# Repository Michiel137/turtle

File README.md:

# Turtle Robot

Een rijdende robot gemaakt met 3D prints, goedkope onderdelen en geprogrammeerd in MicroPython.

Alle bestanden, inclusief deze beschrijving zijn op GitHub te vinden: https://github.com/Michiel137/turtle

## Start

De robot bevat alle bestanden die je nodig hebt, maar hij moet nog wel geconfigureerd worden om hem via WiFi te kunnen programmeren.

1. Sluit de robot met een USB kabel aan op de computer
1. Installeer de ontwikkelomgiving voor MicroPython: [Thonny](https://thonny.org/).
1. Open Thonny. Kies "Standard" voor "Initial Settings"
1. Klik rechtsonderin de statusbalk om de interpreter te configureren
1. Kies "MicroPython (Raspberry Pi Pico)" voor de interpreter
1. Kies "Board in FS mode @ COM..." voor de poort
1. Onderin de shell zie je nu een Python prompt. Je kan hier Python commando's uitvoeren
1. Open in Thonny het bestand boot.py van de robot: Bestand -> Open -> Raspberry Pi Pico -> boot.py
1. Haal van de laatste regel in het bestand de "#" weg en vervang \<SSID\> en \<PASSWORD\> met de WiFi netwerknaam en het WiFi wachtwoord
1. Sla het bestand op: Bestand -> Opslaan
1. Herstart de robot door op het Stop icoon te klikken (of Uitvoeren -> Stoppen/Opnieuw starten backend)
1. De robot maakt nu verbinding met het WiFi netwerk
1. In het shell scherm wordt het adres van de robot geprint achter "WebREPL server started on". Kopieer dit adres
1. Klik rechtsonderin de statusbalk om de interpreter te configureren: Selecteer "Configureren interpreter"
1. Vul bij "Port or WebREPL" het adres van de robot in, maar vervang "http://" door "ws://"
1. Vul voor het wachtwoord "geheim" in
1. OK
1. Thonny maakt nu verbinding via WiFi. De USB kabel is niet meer nodig
1. Op de robot staan een aantal scripts die je uit kan proberen: Bestand -> Open -> Raspberry Pi Pico
    - blink.py - klipper met de leds
    - noise.py - maak geluid
    - collision.py - rij rond en probeer botsingen te voorkomen
    - square.py - teken een vierkant
1. Nadat je het script geopend hebt kan je het met F5 uitvoeren (of Uitvoeren -> Voer huidige script uit)
1. Sommige scripts hebben geen einde. Je kan het script stoppen met Ctrl-C (of Uitvoeren -> Onderbreek uitvoering)
1. Probeer de scripts uit en pas ze aan!
1. Als je een idee hebt en een nieuw script wil maken, maak dan een nieuw bestand: Bestand -> Nieuw
    - Bestanden hoeven niet op de robot te staan om ze uit te voeren: Bestand -> Opslaan -> Deze computer
    - Het is een goed idee om voor een nieuw script te beginnen met een kopie van een bestaand script
    - als je een fout in het script hebt gemaakt wordt dat in het shell scherm getoond als je het script uitvoerd

## Problemen Oplossen

1. Zijn de batterijen leeg?
1. Als de verbinding van Thonny met de robot niet meer lijkt te werken, verbind dan opnieuw door rechtonderin de statusbalk te klikken en "MicroPython (Raspberry Pi Pico) ws://\<ip\>:8266" te kiezen

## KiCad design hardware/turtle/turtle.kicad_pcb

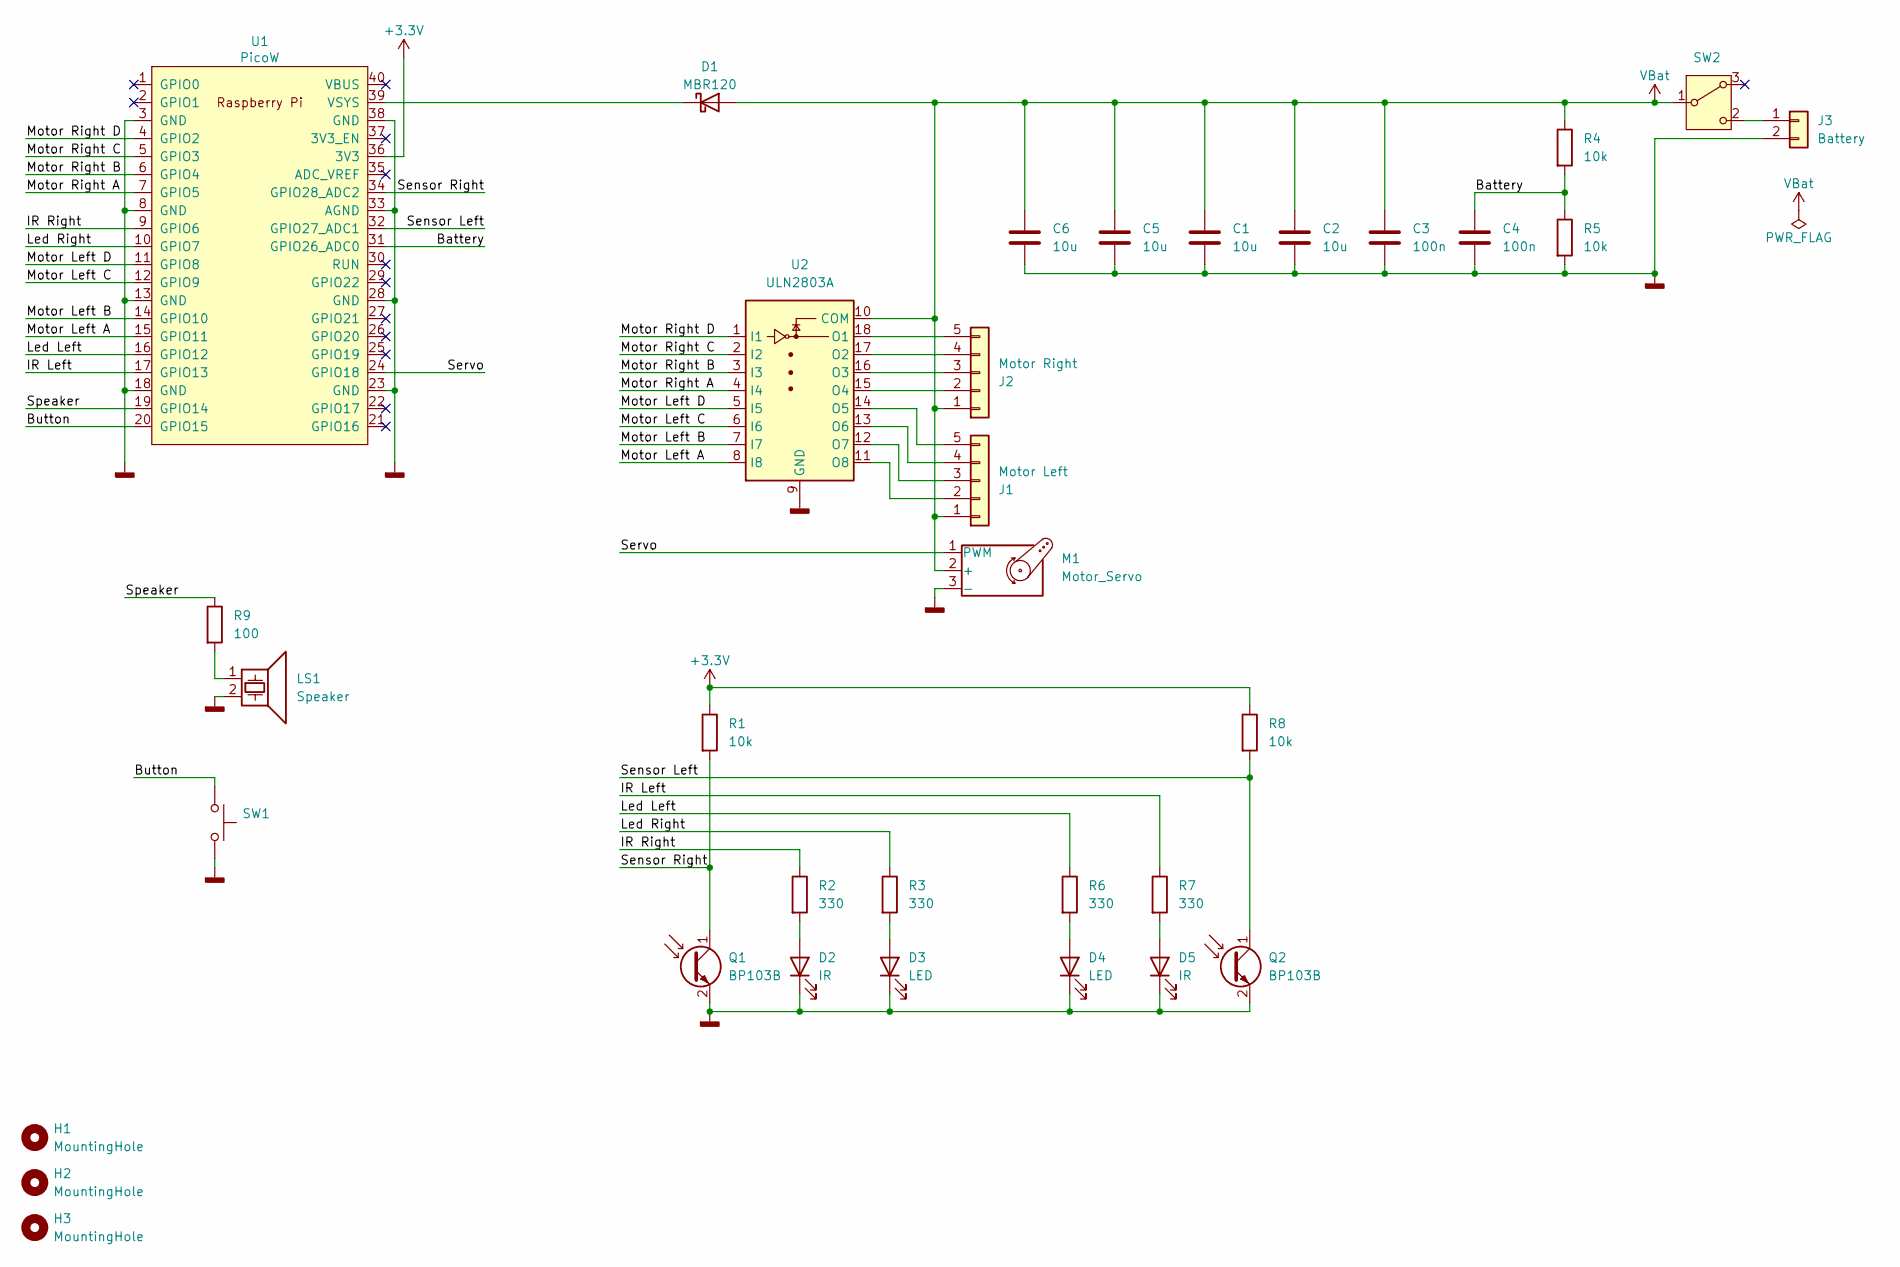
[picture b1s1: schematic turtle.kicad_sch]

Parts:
C1, C2, C5, C6: 10u; C_0603_1608Metric_Pad1.08x0.95mm_HandSolder
C3, C4: 100n; C_0603_1608Metric_Pad1.08x0.95mm_HandSolder
D1: MBR120; D_SOD-123F
D2, D5: IR; LED_D5.0mm_Horizontal_O1.27mm_Z3.0mm_truncated_silkscreen
D3, D4: LED; LED_D5.0mm_Horizontal_O1.27mm_Z3.0mm_truncated_silkscreen
H1, H2, H3: MountingHole; MountingHole_2.2mm_M2
J1: Motor Left; JST_EH_B5B-EH-A_1x05_P2.50mm_Vertical
J2: Motor Right; JST_EH_B5B-EH-A_1x05_P2.50mm_Vertical
J3: Battery; JST_EH_B2B-EH-A_1x02_P2.50mm_Vertical
LS1: Speaker; Buzzer_TDK_PS1240P02BT_D12.2mm_H6.5mm
M1: Motor_Servo; PinHeader_1x03_P2.54mm_Vertical
Q1, Q2: BP103B; LED_D5.0mm_Horizontal_O1.27mm_Z3.0mm_truncated_silkscreen
R1, R4, R5, R8: 10k; R_0603_1608Metric_Pad0.98x0.95mm_HandSolder
R2, R3, R6, R7: 330; R_0603_1608Metric_Pad0.98x0.95mm_HandSolder
R9: 100; R_0603_1608Metric_Pad0.98x0.95mm_HandSolder
SW1: SW_Push; SW_Push_1P1T_NO_CK_KSC6xxJ
SW2: SW_Wuerth_450301014042; SW_Slide-03_Wuerth-WS-SLTV_10x2.5x6.4_P2.54mm
U1: PicoW; RaspberryPi_Pico_Common_THT_stacked
U2: ULN2803A; SOIC-18W_7.5x11.6mm_P1.27mm

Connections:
+3.3V: R1.1, R8.1, U1.36 (3V3)
/Battery: C4.1, R4.2, R5.1, U1.31 (GPIO26_ADC0)
/Button: SW1.1, U1.20 (GPIO15)
/IR Left: R7.1, U1.17 (GPIO13)
/IR Right: R2.1, U1.9 (GPIO6)
/Led Left: R6.1, U1.16 (GPIO12)
/Led Right: R3.1, U1.10 (GPIO7)
/Motor Left A: U1.15 (GPIO11), U2.8 (I8)
/Motor Left B: U1.14 (GPIO10), U2.7 (I7)
/Motor Left C: U1.12 (GPIO9), U2.6 (I6)
/Motor Left D: U1.11 (GPIO8), U2.5 (I5)
/Motor Right A: U1.7 (GPIO5), U2.4 (I4)
/Motor Right B: U1.6 (GPIO4), U2.3 (I3)
/Motor Right C: U1.5 (GPIO3), U2.2 (I2)
/Motor Right D: U1.4 (GPIO2), U2.1 (I1)
/Sensor Left: Q2.1 (C), R8.2, U1.32 (GPIO27_ADC1)
/Sensor Right: Q1.1 (C), R1.2, U1.34 (GPIO28_ADC2)
/Servo: M1.1 (PWM), U1.24 (GPIO18)
/Speaker: R9.1, U1.19 (GPIO14)
GNDD: C1.2, C2.2, C3.2, C4.2, C5.2, C6.2, D2.1 (K), D3.1 (K), D4.1 (K), D5.1 (K), J3.2, LS1.2, M1.3 (-), Q1.2 (E), Q2.2 (E), R5.2, SW1.2, U1.3 (GND), U1.8 (GND), U1.13 (GND), U1.18 (GND), U1.23 (GND), U1.28 (GND), U1.33 (AGND), U1.38 (GND), U2.9 (GND)
unnamed: D1.1 (K), U1.39 (VSYS)
unnamed: D2.2 (A), R2.2
unnamed: D3.2 (A), R3.2
unnamed: D4.2 (A), R6.2
unnamed: D5.2 (A), R7.2
unnamed: J1.2, U2.11 (O8)
unnamed: J1.3, U2.12 (O7)
unnamed: J1.4, U2.13 (O6)
unnamed: J1.5, U2.14 (O5)
unnamed: J2.2, U2.15 (O4)
unnamed: J2.3, U2.16 (O3)
unnamed: J2.4, U2.17 (O2)
unnamed: J2.5, U2.18 (O1)
unnamed: J3.1, SW2.2 (C)
unnamed: LS1.1, R9.2
VBat: C1.1, C2.1, C3.1, C5.1, C6.1, D1.2 (A), J1.1, J2.1, M1.2 (+), R4.1, SW2.1 (B), U2.10 (COM)

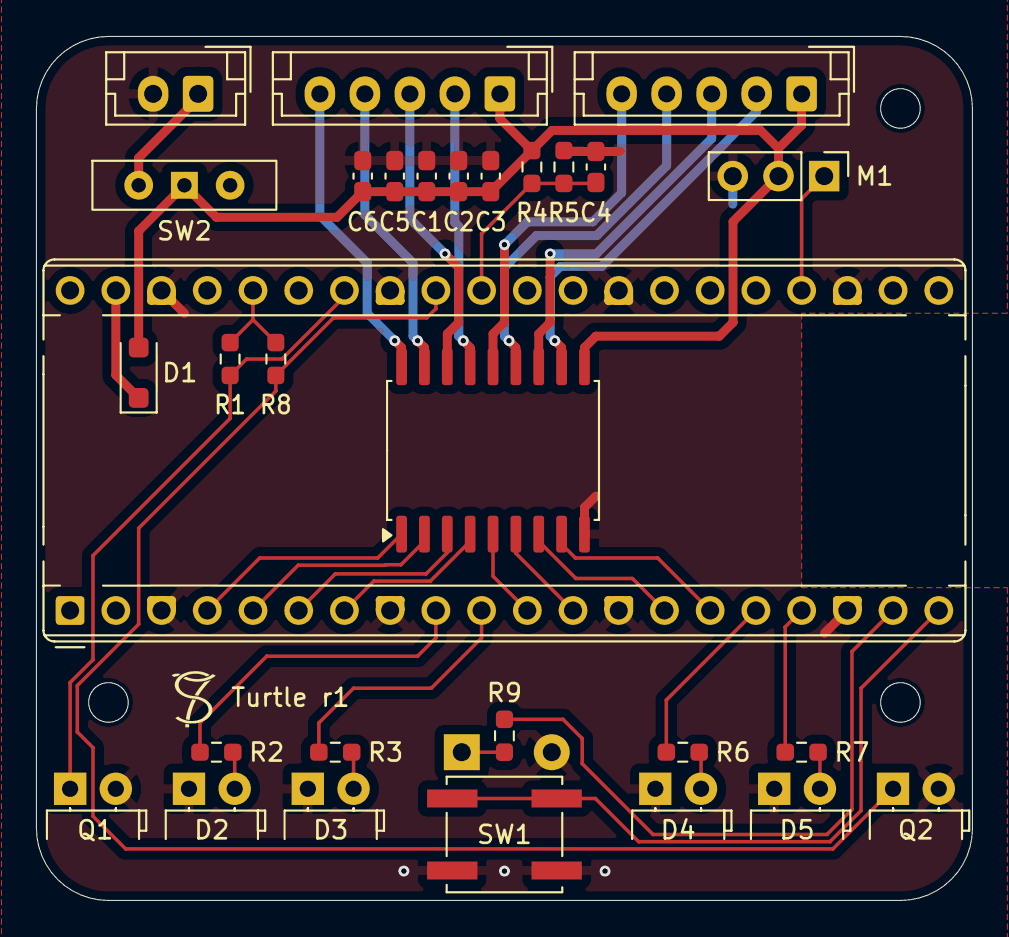
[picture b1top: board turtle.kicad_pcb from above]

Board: 2 copper layers, 52.0 x 48.0 mm, 34 parts (1 on the bottom side), 36 nets.

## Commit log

2025-08-03 Add mechanical parts.
2025-08-03 Add design for electronics.
2025-08-03 Update chassis for new board size.
2025-08-09 Split off parameters and add different components.
2025-08-10 Update for ordered components.
    ULN2803A instead of ULN2803C.
    Speaker with 5mm pitch.
2025-08-10 Add logo and revision to PCB.
2025-08-10 Add revision 1 PCB submitted to JCLPCB for fabrication.
2025-08-27 Move mounting flange of caster to one side.
    This makes room for the battery holder, no matter how large the ball is.
2025-08-28 Make the back side of the collar square.
    This gives a better platform for the servo to push against.
2025-08-29 Add MicroPython library and scripts to control the robot.
2025-08-29 Make the embedded nuts a slightly tighter fit.
2025-08-29 Move mechanics design into separate directory.
2025-08-29 Add LICENSE
2025-08-29 Add README (in Dutch).
2025-08-29 Fix unnumbered lists in README
2025-08-29 Fix ip address placeholder in README.
